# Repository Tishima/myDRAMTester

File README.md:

# my DRAMTester for 4164 and 41256 DRAM

DRAMduino

The DRAMTester shield is a Arduino UNO shield , to test DRAM 4164 and 41256 .
It check the DRAM with diffrent read/write operations

Its based on the work on
https://forum.defence-force.org/viewtopic.php?t=1699

This repository contains all eagle files, gerber file, BOM, schematics

Depending on where the parts and pcbs are purchased, the price for the complete shield is around 6€ (2023), without Arduino UNO and power supply
I built this project, because the PCB on PCBWay has to small holes for all ZIF Sockets

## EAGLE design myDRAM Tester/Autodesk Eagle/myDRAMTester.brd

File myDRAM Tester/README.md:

# my DRAMTester for 4164 and 41256 DRAM
The DRAMTester shield is a Arduino UNO shield , to test DRAM 4164 and 41256 .
It check the DRAM with diffrent read/write operations

Its based on the work on
https://forum.defence-force.org/viewtopic.php?t=1699

This repository contains all eagle files, gerber file, BOM, schematics

Depending on where the parts and pcbs are purchased, the price for the complete shield is around 6€ (2023), without Arduino UNO and power supply
I built this project, because the PCB on PCBWay has to small holes for all ZIF Sockets

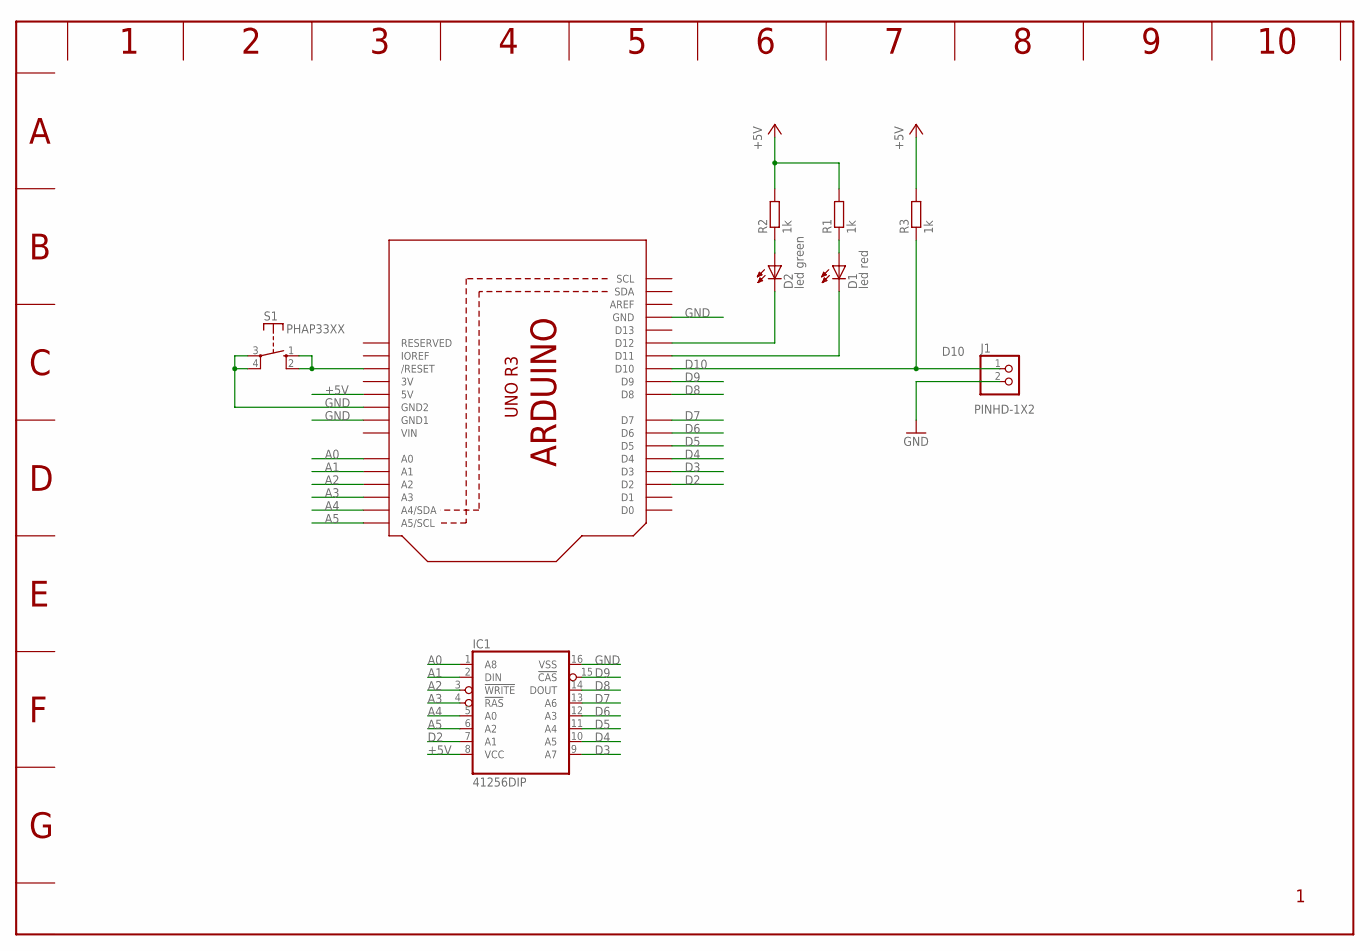
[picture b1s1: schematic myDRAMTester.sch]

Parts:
D1: led red; LED3MM
D2: led green; LED3MM
IC1: 41256DIP; DIL16
J1: PINHD-1X2; 1X02
R1, R2, R3: 1k; 0207/10
S1: PHAP33XX
U2: ARDUINOR3_BBSMALL; ARDUINOR3S

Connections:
3V: U2.3V
+5V: IC1.8 (VCC), R1.2, R2.2, R3.2, U2.5V
A0: IC1.1 (A8), U2.A0
A1: IC1.2 (DIN), U2.A1
A2: IC1.3 (!WRITE), U2.A2
A3: IC1.4 (!RAS), U2.A3
A4: IC1.5 (A0), U2.A4 (A4/SDA)
A5: IC1.6 (A2), U2.A5 (A5/SCL)
D2: IC1.7 (A1), U2.D2
D3: IC1.9 (A7), U2.D3
D4: IC1.10 (A5), U2.D4
D5: IC1.11 (A4), U2.D5
D6: IC1.12 (A3), U2.D6
D7: IC1.13 (A6), U2.D7
D8: IC1.14 (DOUT), U2.D8
D9: IC1.15 (!CAS), U2.D9
D10: J1.1, R3.1, U2.D10
GND: IC1.16 (VSS), J1.2, S1.3, S1.4, U2.GND, U2.GND1, U2.GND2
unnamed: D2.K (C), U2.D12
unnamed: D1.K (C), U2.D11
unnamed: D2.A, R2.1
unnamed: D1.A, R1.1
unnamed: S1.1 (S), S1.2 (S), U2.RESET (/RESET)
VIN: U2.VIN

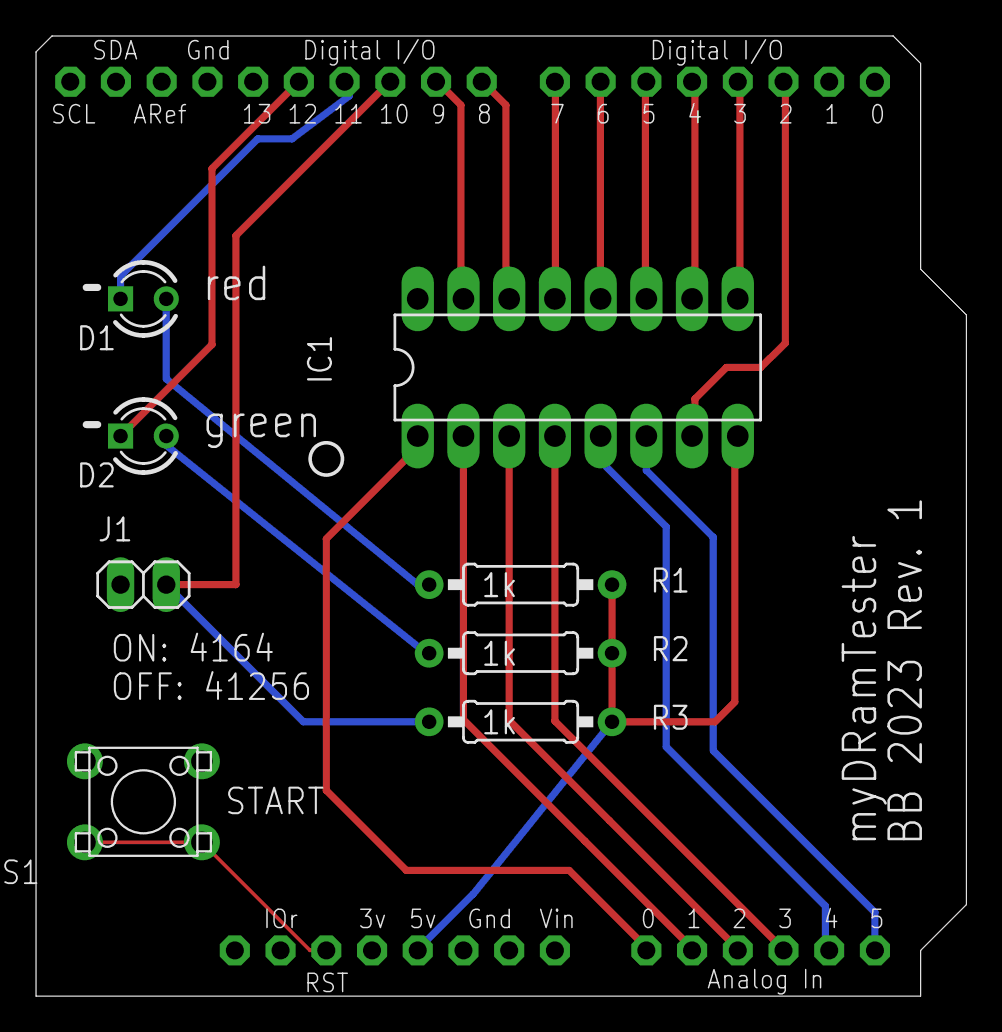
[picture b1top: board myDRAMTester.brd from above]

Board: 2 copper layers, 51.7 x 53.3 mm, 9 parts (0 on the bottom side), 22 nets.
